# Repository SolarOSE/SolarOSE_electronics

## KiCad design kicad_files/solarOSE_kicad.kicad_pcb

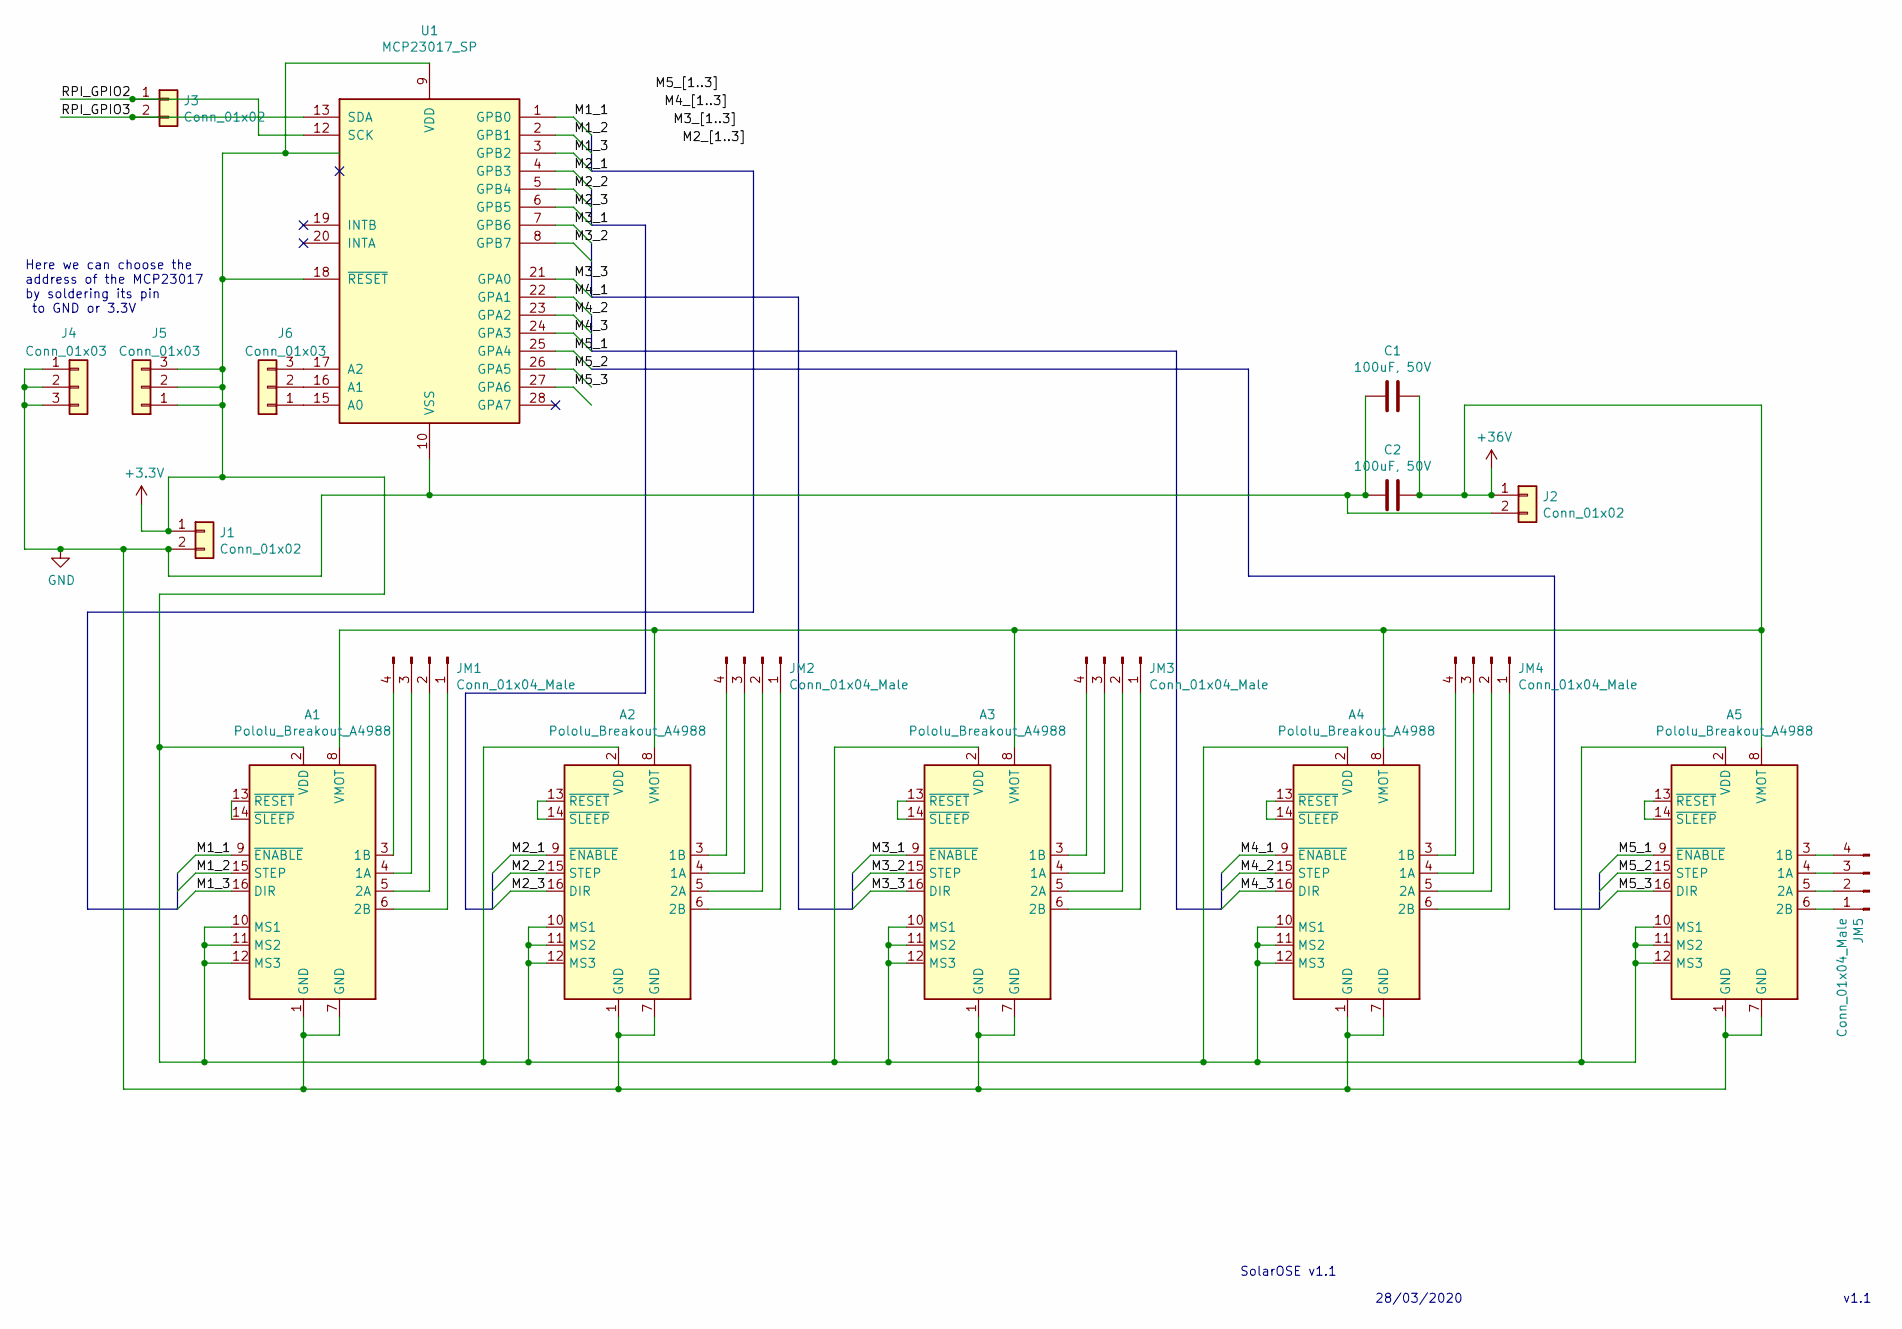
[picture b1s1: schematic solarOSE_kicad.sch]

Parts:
A1, A2, A3, A4, A5: Pololu_Breakout_A4988; Pololu_Breakout-16_15.2x20.3mm
C1, C2: 100uF, 50V; CP_Radial_D8.0mm_P3.50mm
J1, J3: Conn_01x02; SolderWirePad_1x02_P3.81mm_Drill1mm
J2: Conn_01x02; SolderWirePad_1x02_P7.62mm_Drill2mm
J4, J5, J6: Conn_01x03; SolderWirePad_1x03_P3.81mm_Drill1.2mm
JM1, JM2, JM3, JM4, JM5: Conn_01x04_Male; SolderWirePad_1x04_P6.35mm_Drill2mm
U1: MCP23017_SP; DIP-28_W7.62mm

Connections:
+3V3: A1.2 (VDD), A1.10 (MS1), A1.11 (MS2), A1.12 (MS3), A2.2 (VDD), A2.10 (MS1), A2.11 (MS2), A2.12 (MS3), A3.2 (VDD), A3.10 (MS1), A3.11 (MS2), A3.12 (MS3), A4.2 (VDD), A4.10 (MS1), A4.11 (MS2), A4.12 (MS3), A5.2 (VDD), A5.10 (MS1), A5.11 (MS2), A5.12 (MS3), J1.1, J5.1, J5.2, J5.3, U1.9 (VDD), U1.11 (NC), U1.18 (~RESET~)
+36V: A1.8 (VMOT), A2.8 (VMOT), A3.8 (VMOT), A4.8 (VMOT), A5.8 (VMOT), C1.1, C2.1, J2.1
/M1_1: A1.9 (~ENABLE), U1.1 (GPB0)
/M1_2: A1.15 (STEP), U1.2 (GPB1)
/M1_3: A1.16 (DIR), U1.3 (GPB2)
/M2_1: A2.9 (~ENABLE), U1.4 (GPB3)
/M2_2: A2.15 (STEP), U1.5 (GPB4)
/M2_3: A2.16 (DIR), U1.6 (GPB5)
/M3_1: A3.9 (~ENABLE), U1.7 (GPB6)
/M3_2: A3.15 (STEP), U1.8 (GPB7)
/M3_3: A3.16 (DIR), U1.21 (GPA0)
/M4_1: A4.9 (~ENABLE), U1.22 (GPA1)
/M4_2: A4.15 (STEP), U1.23 (GPA2)
/M4_3: A4.16 (DIR), U1.24 (GPA3)
/M5_1: A5.9 (~ENABLE), U1.25 (GPA4)
/M5_2: A5.15 (STEP), U1.26 (GPA5)
/M5_3: A5.16 (DIR), U1.27 (GPA6)
/RPI_GPIO2: J3.1, U1.12 (SCK)
/RPI_GPIO3: J3.2, U1.13 (SDA)
GND: A1.1 (GND), A1.7 (GND), A2.1 (GND), A2.7 (GND), A3.1 (GND), A3.7 (GND), A4.1 (GND), A4.7 (GND), A5.1 (GND), A5.7 (GND), C1.2, C2.2, J1.2, J2.2, J4.1, J4.2, J4.3, U1.10 (VSS)
unnamed: A1.3 (1B), JM1.4
unnamed: A1.4 (1A), JM1.3
unnamed: A1.5 (2A), JM1.2
unnamed: A1.6 (2B), JM1.1
unnamed: A1.13 (~RESET), A1.14 (~SLEEP)
unnamed: A2.3 (1B), JM2.4
unnamed: A2.4 (1A), JM2.3
unnamed: A2.5 (2A), JM2.2
unnamed: A2.6 (2B), JM2.1
unnamed: A2.13 (~RESET), A2.14 (~SLEEP)
unnamed: A3.3 (1B), JM3.4
unnamed: A3.4 (1A), JM3.3
unnamed: A3.5 (2A), JM3.2
unnamed: A3.6 (2B), JM3.1
unnamed: A3.13 (~RESET), A3.14 (~SLEEP)
unnamed: A4.3 (1B), JM4.4
unnamed: A4.4 (1A), JM4.3
unnamed: A4.5 (2A), JM4.2
unnamed: A4.6 (2B), JM4.1
unnamed: A4.13 (~RESET), A4.14 (~SLEEP)
unnamed: A5.3 (1B), JM5.4
unnamed: A5.4 (1A), JM5.3
unnamed: A5.5 (2A), JM5.2
unnamed: A5.6 (2B), JM5.1
unnamed: A5.13 (~RESET), A5.14 (~SLEEP)
unnamed: J6.1, U1.15 (A0)
unnamed: J6.2, U1.16 (A1)
unnamed: J6.3, U1.17 (A2)

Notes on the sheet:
Here we can choose the address of the MCP23017 by soldering its pin to GND or 3.3V
SolarOSE v1.1
28/03/2020
v1.1

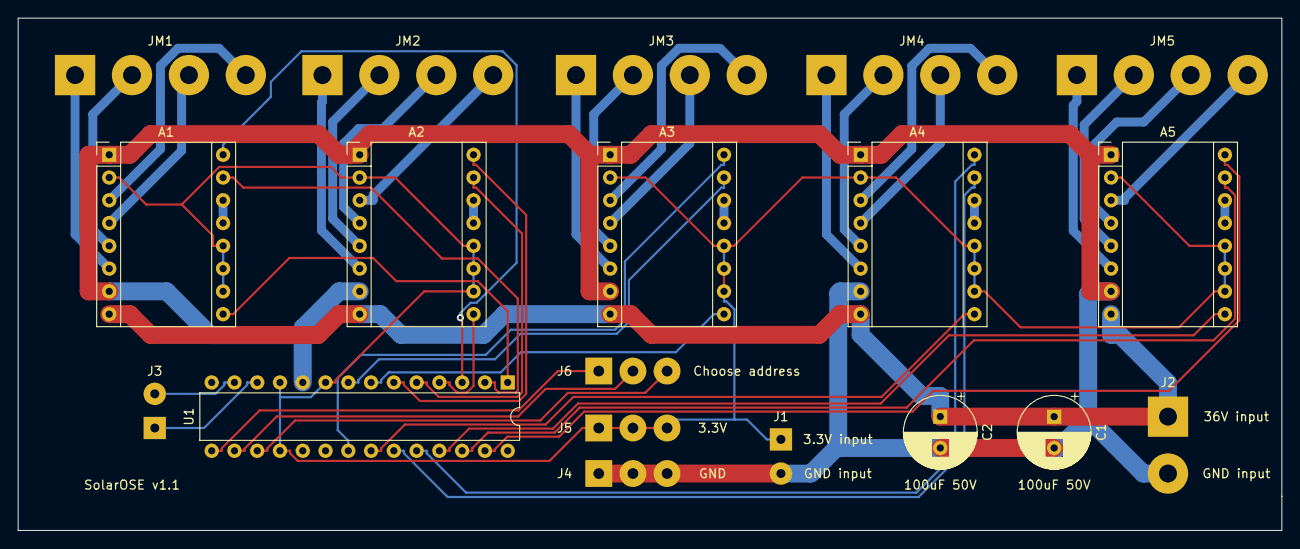
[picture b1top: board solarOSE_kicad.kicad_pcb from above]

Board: 2 copper layers, 141.0 x 57.2 mm, 19 parts (0 on the bottom side), 48 nets.

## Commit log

2020-03-14 pushing first version of PCB
2020-03-28 version with one card for 5 motors
